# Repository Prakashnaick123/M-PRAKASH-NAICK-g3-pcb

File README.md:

# M-PRAKASH-NAICK-g3-pcb
Prakashnaick123

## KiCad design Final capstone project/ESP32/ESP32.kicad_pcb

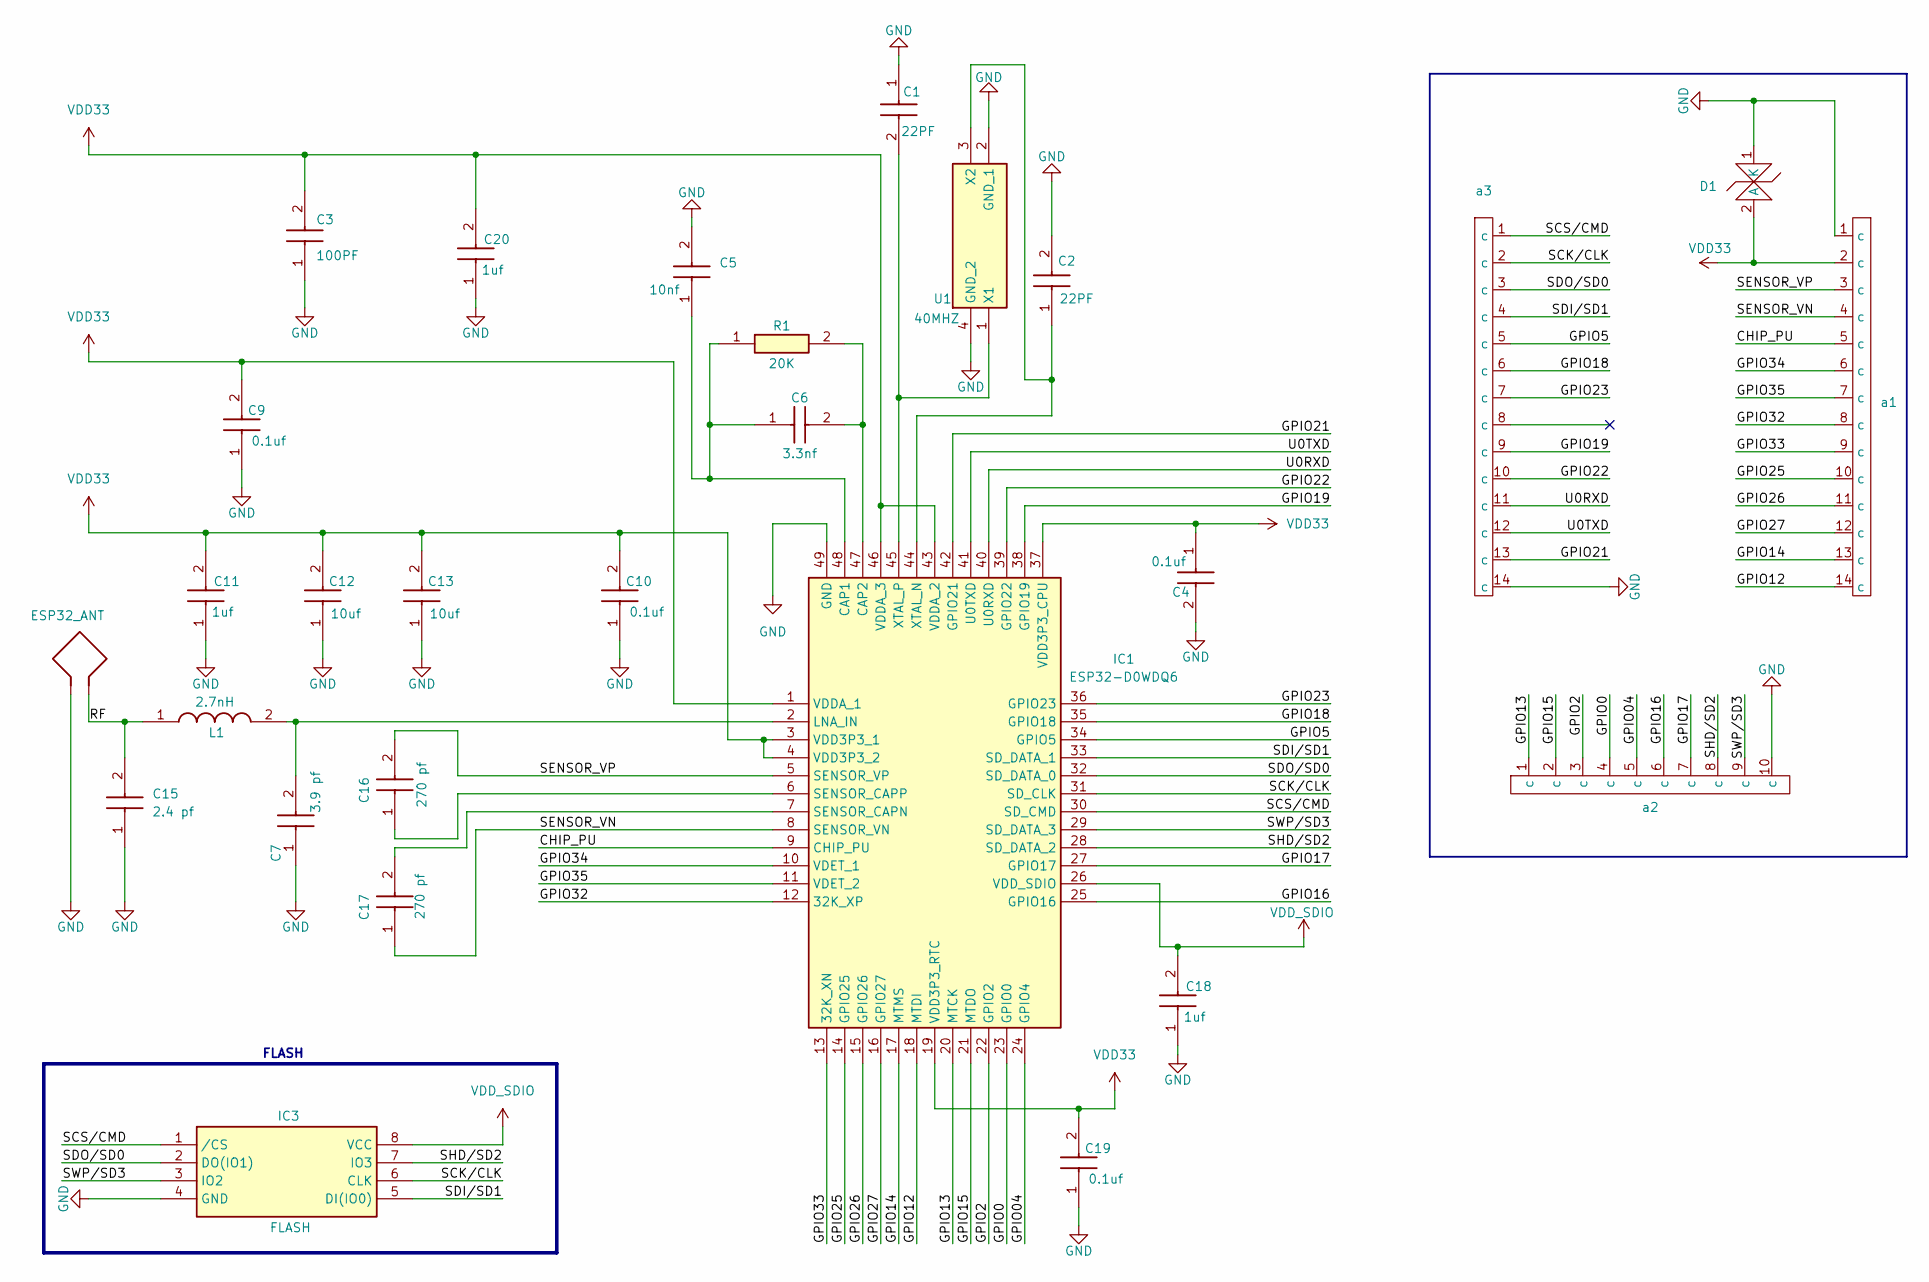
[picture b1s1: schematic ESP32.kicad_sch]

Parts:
AE1: ESP32_ANT
C1, C2: 22PF; GRM0335C1H220JA01D; Manufacturer_Part_Number GRM0335C1H220JA01D; Mouser Part Number 81-GRM0335C1H220JA1D
C3: 100PF; GRM0335C1H101JA01D; Manufacturer_Part_Number GRM0335C1H101JA01D; Mouser Part Number 81-GRM0335C1H101JA1D
C4, C9, C10, C19: 0.1uf; GRM033C81E104KE14D; Manufacturer_Part_Number GRM033C81E104KE14D; Mouser Part Number 81-GRM33C81E104KE14D
C5: 10nf; MSASJ021SB5103KWNA01; Manufacturer_Part_Number MSASJ021SB5103KWNA01
C6: 3.3nf; GRM022R60J332KE19L; Manufacturer_Part_Number GRM022R60J332KE19L
C7: 3.9 pf; GRM0335C1H3R9BA01D; Manufacturer_Part_Number GRM0335C1H3R9BA01D; Mouser Part Number 81-GRM0335C1H3R9BA1D
C11, C18, C20: 1uf; GRM033R60J105MEA2D; Manufacturer_Part_Number GRM033R60J105MEA2D; Mouser Part Number 81-GRM033R60J105ME2D
C12, C13: 10uf; GRM21BR61E106KA73L; Manufacturer_Part_Number GRM21BR61E106KA73L; Mouser Part Number 81-GRM21BR61E106KA3L
C15: 2.4 pf; GRM0335C1H2R4BA01D; Manufacturer_Part_Number GRM0335C1H2R4BA01D; Mouser Part Number 81-GRM0335C1H2R4BA1D
C16, C17: 270 pf; GRM033R71E271KA01D; Manufacturer_Part_Number GRM033R71E271KA01D
D1: ESD3.3V88D-C
IC1: ESP32-D0WDQ6; Manufacturer_Part_Number ESP32-D0WDQ6; Mouser Part Number 356-ESP32-D0WDQ6
IC3: FLASH; W25Q32JVSSIQ_TR; Manufacturer_Part_Number W25Q32JVSSIQ TR; Mouser Part Number 454-W25Q32JVSSIQTR
L1: 2.7nH; AIMC-0603-2N7S-T; Manufacturer_Part_Number AIMC-0603-2N7S-T; Mouser Part Number 815-AIMC-0603-2N7ST
R1: 20K; ERJ-XGNJ203Y; Manufacturer_Part_Number ERJ-XGNJ203Y; Mouser Part Number 667-ERJ-XGNJ203Y
U1: 40MHZ; ABM11W-40.0000MHZ-4-B1U-T3; Manufacturer_Part_Number ABM11W-40.0000MHZ-4-B1U-T3; Mouser Part Number 815-11W40-4B1UT
a1: cas_hol_esp32_1
a2: cas_hol_esp32_2
a3: cas_hol_esp32_3

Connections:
/CHIP_PU: IC1.9 (CHIP_PU), a1.5 (c)
/GPIO0: IC1.23 (GPIO0), a2.4 (c)
/GPIO2: IC1.22 (GPIO2), a2.3 (c)
/GPIO04: IC1.24 (GPIO4), a2.5 (c)
/GPIO5: IC1.34 (GPIO5), a3.5 (c)
/GPIO12: IC1.18 (MTDI), a1.14 (c)
/GPIO13: IC1.20 (MTCK), a2.1 (c)
/GPIO14: IC1.17 (MTMS), a1.13 (c)
/GPIO15: IC1.21 (MTDO), a2.2 (c)
/GPIO16: IC1.25 (GPIO16), a2.6 (c)
/GPIO17: IC1.27 (GPIO17), a2.7 (c)
/GPIO18: IC1.35 (GPIO18), a3.6 (c)
/GPIO19: IC1.38 (GPIO19), a3.9 (c)
/GPIO21: IC1.42 (GPIO21), a3.13 (c)
/GPIO22: IC1.39 (GPIO22), a3.10 (c)
/GPIO23: IC1.36 (GPIO23), a3.7 (c)
/GPIO25: IC1.14 (GPIO25), a1.10 (c)
/GPIO26: IC1.15 (GPIO26), a1.11 (c)
/GPIO27: IC1.16 (GPIO27), a1.12 (c)
/GPIO32: IC1.12 (32K_XP), a1.8 (c)
/GPIO33: IC1.13 (32K_XN), a1.9 (c)
/GPIO34: IC1.10 (VDET_1), a1.6 (c)
/GPIO35: IC1.11 (VDET_2), a1.7 (c)
/RF: AE1.1, C15.2, L1.1
/SCK/CLK: IC1.31 (SD_CLK), IC3.6 (CLK), a3.2 (c)
/SCS/CMD: IC1.30 (SD_CMD), IC3.1 (/CS), a3.1 (c)
/SDI/SD1: IC1.33 (SD_DATA_1), IC3.5 (DI(IO0)), a3.4 (c)
/SDO/SD0: IC1.32 (SD_DATA_0), IC3.2 (DO(IO1)), a3.3 (c)
/SENSOR_VN: C17.1, IC1.8 (SENSOR_VN), a1.4 (c)
/SENSOR_VP: C16.2, IC1.5 (SENSOR_VP), a1.3 (c)
/SHD/SD2: IC1.28 (SD_DATA_2), IC3.7 (IO3), a2.8 (c)
/SWP/SD3: IC1.29 (SD_DATA_3), IC3.3 (IO2), a2.9 (c)
/U0RXD: IC1.40 (U0RXD), a3.11 (c)
/U0TXD: IC1.41 (U0TXD), a3.12 (c)
GND: AE1.2, C1.1, C2.2, C3.1, C4.2, C5.2, C7.1, C9.1, C10.1, C11.1, C12.1, C13.1, C15.1, C18.1, C19.1, C20.1, D1.1 (K), IC1.49 (GND), IC3.4 (GND), U1.2 (GND_1), U1.4 (GND_2), a1.1 (c), a2.10 (c), a3.14 (c)
unnamed: C5.1, C6.1, IC1.48 (CAP1), R1.1
unnamed: C6.2, IC1.47 (CAP2), R1.2
unnamed: C7.2, IC1.2 (LNA_IN), L1.2
unnamed: C17.2, IC1.7 (SENSOR_CAPN)
unnamed: C16.1, IC1.6 (SENSOR_CAPP)
unnamed: C2.1, IC1.44 (XTAL_N), U1.3 (X2)
unnamed: C1.2, IC1.45 (XTAL_P), U1.1 (X1)
VDD33: C3.2, C4.1, C9.2, C10.2, C11.2, C12.2, C13.2, C19.2, C20.2, D1.2 (A), IC1.1 (VDDA_1), IC1.3 (VDD3P3_1), IC1.4 (VDD3P3_2), IC1.19 (VDD3P3_RTC), IC1.37 (VDD3P3_CPU), IC1.43 (VDDA_2), IC1.46 (VDDA_3), a1.2 (c)
VDD_SDIO: C18.2, IC1.26 (VDD_SDIO), IC3.8 (VCC)

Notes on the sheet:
FLASH

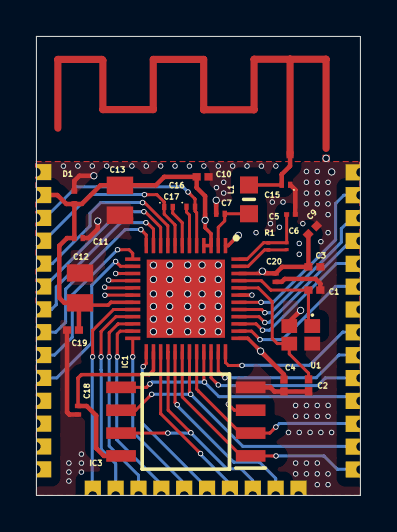
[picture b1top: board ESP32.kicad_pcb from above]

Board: 4 copper layers, 18.0 x 25.5 mm, 28 parts (0 on the bottom side), 44 nets.
